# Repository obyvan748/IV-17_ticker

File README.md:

# IV-17_Ticker

## A ticker build from IV-17 tubes in a stackable manner

The idea is to build a ticker from IV-17 tubes wich should be able to be stacked to support a variable number of tube modules.

The ticker is made up from a main component und many client components. 
The main component give the high voltage power supply and the server component a home. 
The client components are made up from a tube and a dasy chanable electronic to drive the tube.

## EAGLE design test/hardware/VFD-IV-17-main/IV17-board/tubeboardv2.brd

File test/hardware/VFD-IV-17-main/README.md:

# VFD-IV-17
Schematics, board, and code for IV-17

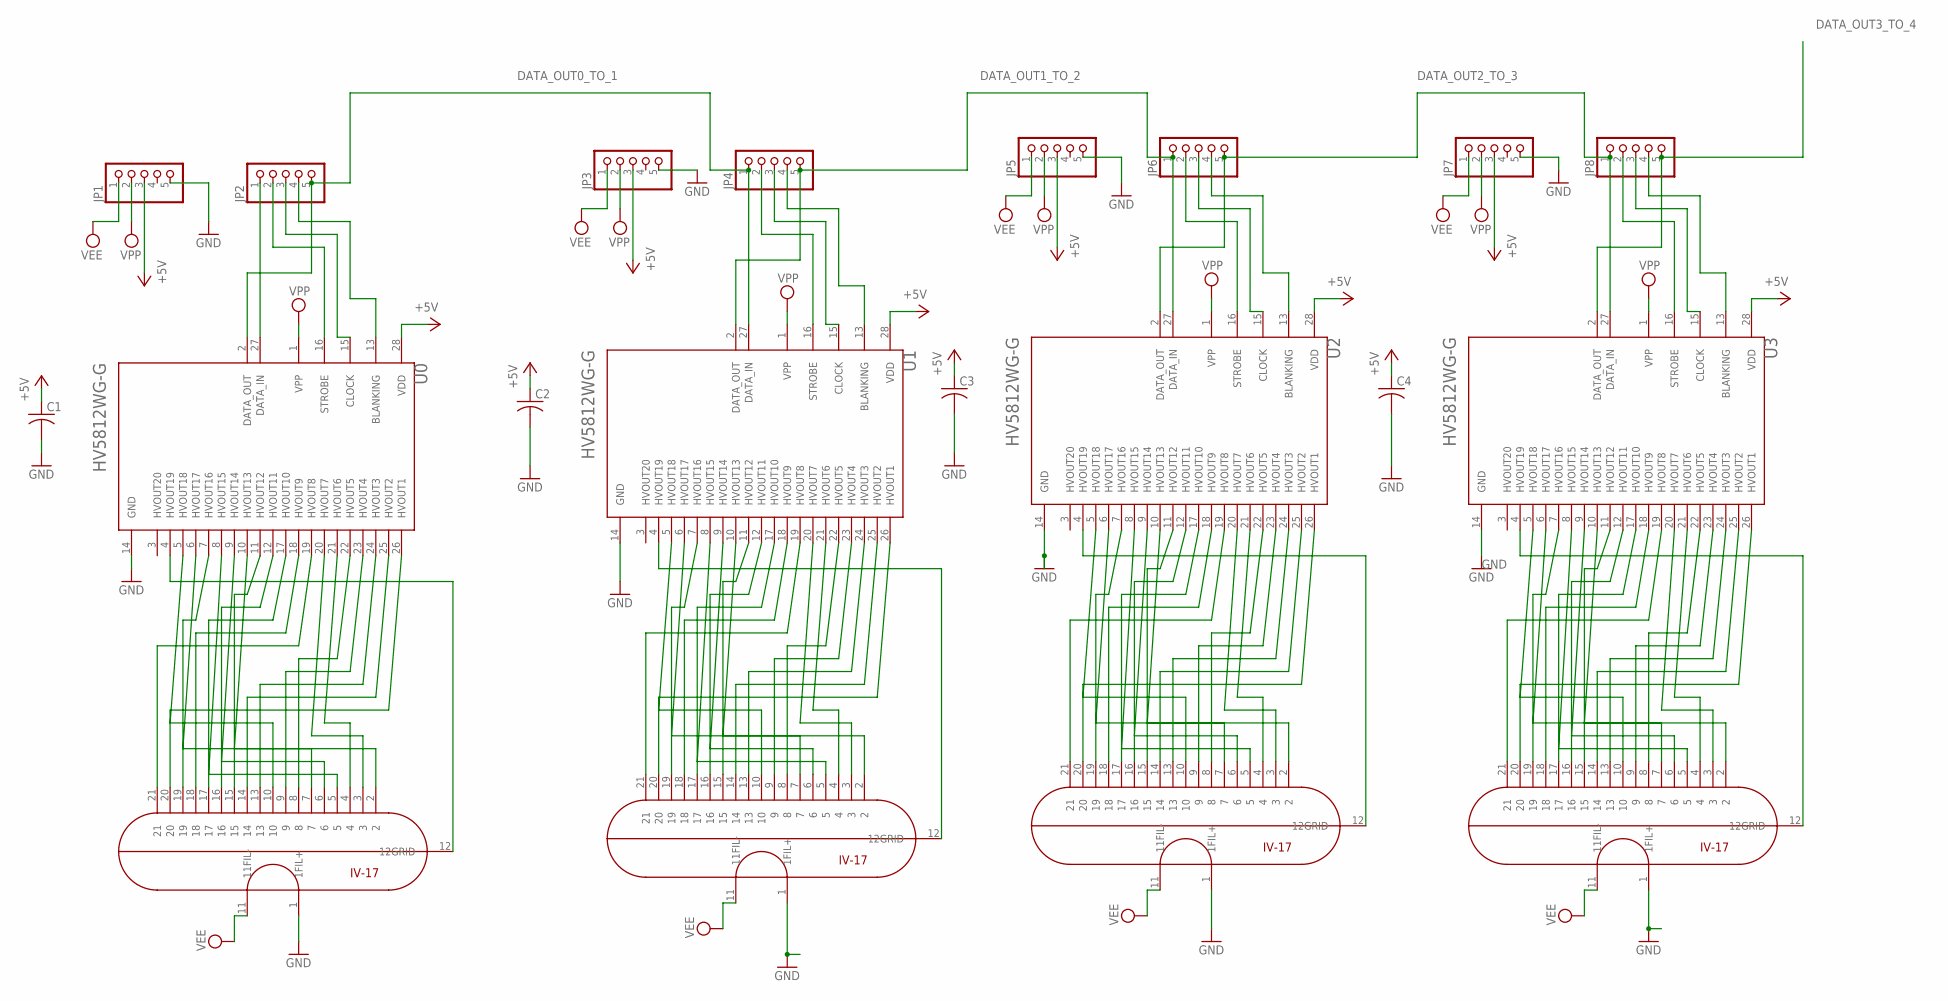
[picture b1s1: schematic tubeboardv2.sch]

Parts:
C1, C2, C3, C4: C-USC0805; C0805
IV0, IV1, IV2, IV3: IV17; NIXIE-22
JP1, JP2, JP3, JP4, JP5, JP6, JP7, JP8: PINHD-1X5; 1X05
U0, U1, U2, U3: MICROCHIP_HV5812WG-GMICROCHIP_HV5812WG-G_0_0; MICROCHIP_HV5812WG-G_0

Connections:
+5V: C1.1, C2.1, C3.1, C4.1, JP1.3, JP3.3, JP5.3, JP7.3, U0.28 (VDD), U1.28 (VDD), U2.28 (VDD), U3.28 (VDD)
BLANK: JP2.4, JP4.4, JP6.4, JP8.4, U0.13 (BLANKING), U1.13 (BLANKING), U2.13 (BLANKING), U3.13 (BLANKING)
CLOCK: JP2.3, JP4.3, JP6.3, JP8.3, U0.15 (CLOCK), U1.15 (CLOCK), U2.15 (CLOCK), U3.15 (CLOCK)
DATA_IN: JP2.1, U0.27 (DATA_IN)
DATA_OUT0_TO_1: JP2.5, JP4.1, U0.2 (DATA_OUT), U1.27 (DATA_IN)
DATA_OUT1_TO_2: JP4.5, JP6.1, U1.2 (DATA_OUT), U2.27 (DATA_IN)
DATA_OUT2_TO_3: JP6.5, JP8.1, U2.2 (DATA_OUT), U3.27 (DATA_IN)
DATA_OUT3_TO_4: JP8.5, U3.2 (DATA_OUT)
GND: C1.2, C2.2, C3.2, C4.2, IV0.1 (1FIL+), IV1.1 (1FIL+), IV2.1 (1FIL+), IV3.1 (1FIL+), JP1.5, JP3.5, JP5.5, JP7.5, U0.14 (GND), U1.14 (GND), U2.14 (GND), U3.14 (GND)
unnamed: IV0.20, U0.26 (HVOUT1)
unnamed: IV0.14, U0.25 (HVOUT2)
unnamed: IV0.13, U0.24 (HVOUT3)
unnamed: IV0.9, U0.23 (HVOUT4)
unnamed: IV0.8, U0.22 (HVOUT5)
unnamed: IV0.4, U0.21 (HVOUT6)
unnamed: IV0.3, U0.20 (HVOUT7)
unnamed: IV0.21, U0.19 (HVOUT8)
unnamed: IV0.18, U0.18 (HVOUT9)
unnamed: IV0.17, U0.17 (HVOUT10)
unnamed: IV0.16, U0.12 (HVOUT11)
unnamed: IV0.15, U0.11 (HVOUT12)
unnamed: IV0.7, U0.10 (HVOUT13)
unnamed: IV0.6, U0.9 (HVOUT14)
unnamed: IV0.5, U0.8 (HVOUT15)
unnamed: IV0.19, U0.7 (HVOUT16)
unnamed: IV0.2, U0.6 (HVOUT17)
unnamed: IV0.10, U0.5 (HVOUT18)
unnamed: IV0.12 (12GRID), U0.4 (HVOUT19)
unnamed: IV1.20, U1.26 (HVOUT1)
unnamed: IV1.14, U1.25 (HVOUT2)
unnamed: IV1.13, U1.24 (HVOUT3)
unnamed: IV1.9, U1.23 (HVOUT4)
unnamed: IV1.8, U1.22 (HVOUT5)
unnamed: IV1.4, U1.21 (HVOUT6)
unnamed: IV1.3, U1.20 (HVOUT7)
unnamed: IV1.21, U1.19 (HVOUT8)
unnamed: IV1.18, U1.18 (HVOUT9)
unnamed: IV1.17, U1.17 (HVOUT10)
unnamed: IV1.16, U1.12 (HVOUT11)
unnamed: IV1.15, U1.11 (HVOUT12)
unnamed: IV1.7, U1.10 (HVOUT13)
unnamed: IV1.6, U1.9 (HVOUT14)
unnamed: IV1.5, U1.8 (HVOUT15)
unnamed: IV1.19, U1.7 (HVOUT16)
unnamed: IV1.2, U1.6 (HVOUT17)
unnamed: IV1.10, U1.5 (HVOUT18)
unnamed: IV1.12 (12GRID), U1.4 (HVOUT19)
unnamed: IV2.20, U2.26 (HVOUT1)
unnamed: IV2.14, U2.25 (HVOUT2)
unnamed: IV2.13, U2.24 (HVOUT3)
unnamed: IV2.9, U2.23 (HVOUT4)
unnamed: IV2.8, U2.22 (HVOUT5)
unnamed: IV2.4, U2.21 (HVOUT6)
unnamed: IV2.3, U2.20 (HVOUT7)
unnamed: IV2.21, U2.19 (HVOUT8)
unnamed: IV2.18, U2.18 (HVOUT9)
unnamed: IV2.17, U2.17 (HVOUT10)
unnamed: IV2.16, U2.12 (HVOUT11)
unnamed: IV2.15, U2.11 (HVOUT12)
unnamed: IV2.7, U2.10 (HVOUT13)
unnamed: IV2.6, U2.9 (HVOUT14)
unnamed: IV2.5, U2.8 (HVOUT15)
unnamed: IV2.19, U2.7 (HVOUT16)
unnamed: IV2.2, U2.6 (HVOUT17)
unnamed: IV2.10, U2.5 (HVOUT18)
unnamed: IV2.12 (12GRID), U2.4 (HVOUT19)
unnamed: IV3.20, U3.26 (HVOUT1)
unnamed: IV3.14, U3.25 (HVOUT2)
unnamed: IV3.13, U3.24 (HVOUT3)
unnamed: IV3.9, U3.23 (HVOUT4)
unnamed: IV3.8, U3.22 (HVOUT5)
unnamed: IV3.4, U3.21 (HVOUT6)
unnamed: IV3.3, U3.20 (HVOUT7)
unnamed: IV3.21, U3.19 (HVOUT8)
unnamed: IV3.18, U3.18 (HVOUT9)
unnamed: IV3.17, U3.17 (HVOUT10)
unnamed: IV3.16, U3.12 (HVOUT11)
unnamed: IV3.15, U3.11 (HVOUT12)
unnamed: IV3.7, U3.10 (HVOUT13)
unnamed: IV3.6, U3.9 (HVOUT14)
unnamed: IV3.5, U3.8 (HVOUT15)
unnamed: IV3.19, U3.7 (HVOUT16)
unnamed: IV3.2, U3.6 (HVOUT17)
unnamed: IV3.10, U3.5 (HVOUT18)
unnamed: IV3.12 (12GRID), U3.4 (HVOUT19)
STROBE: JP2.2, JP4.2, JP6.2, JP8.2, U0.16 (STROBE), U1.16 (STROBE), U2.16 (STROBE), U3.16 (STROBE)
VEE: IV0.11 (11FIL-), IV1.11 (11FIL-), IV2.11 (11FIL-), IV3.11 (11FIL-), JP1.1, JP3.1, JP5.1, JP7.1
VPP: JP1.2, JP3.2, JP5.2, JP7.2, U0.1 (VPP), U1.1 (VPP), U2.1 (VPP), U3.1 (VPP)

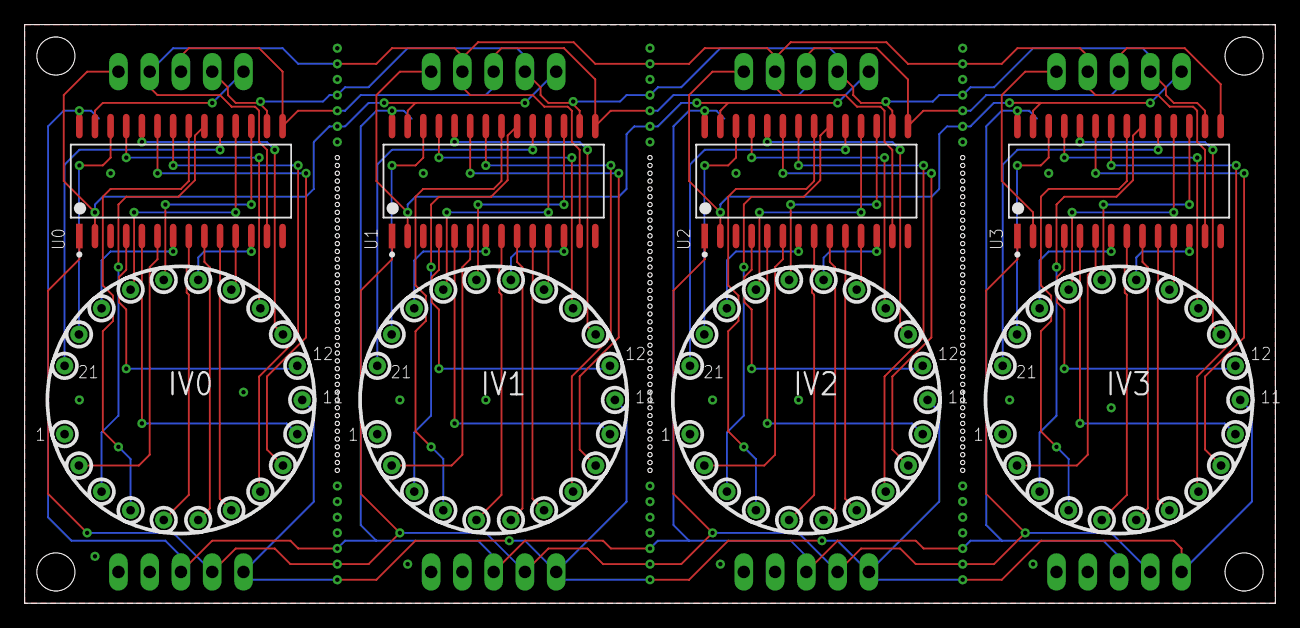
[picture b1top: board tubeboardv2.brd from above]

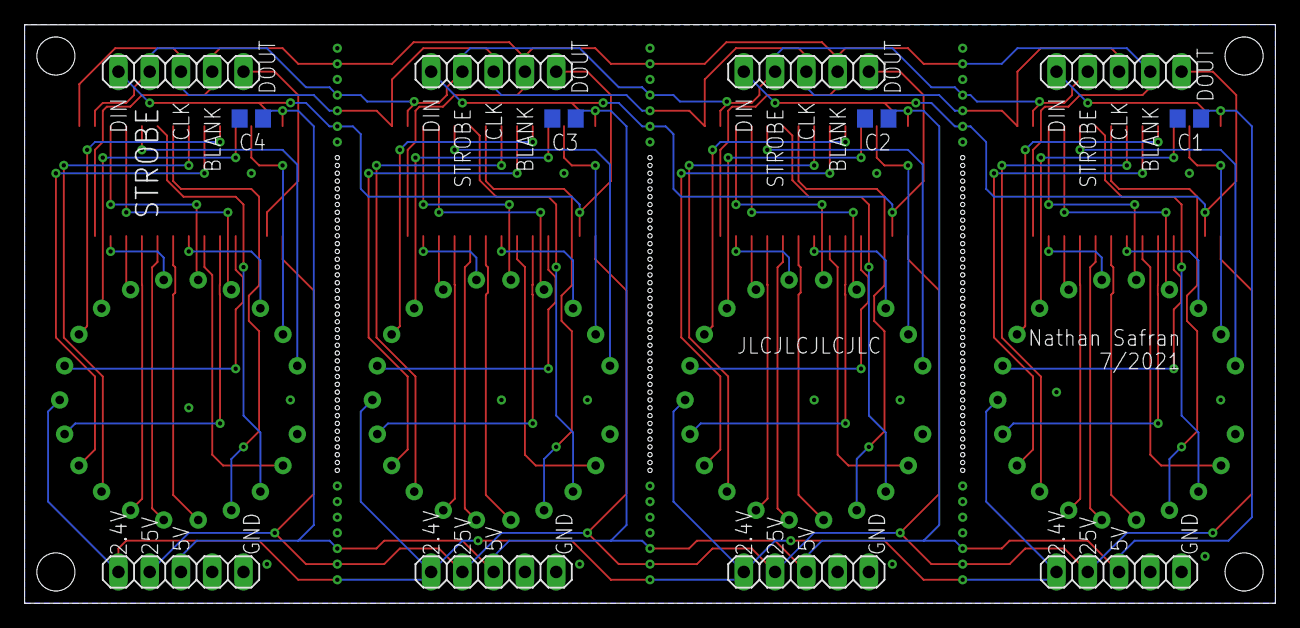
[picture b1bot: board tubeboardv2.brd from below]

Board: 2 copper layers, 101.6 x 47.0 mm, 20 parts (12 on the bottom side), 88 nets.

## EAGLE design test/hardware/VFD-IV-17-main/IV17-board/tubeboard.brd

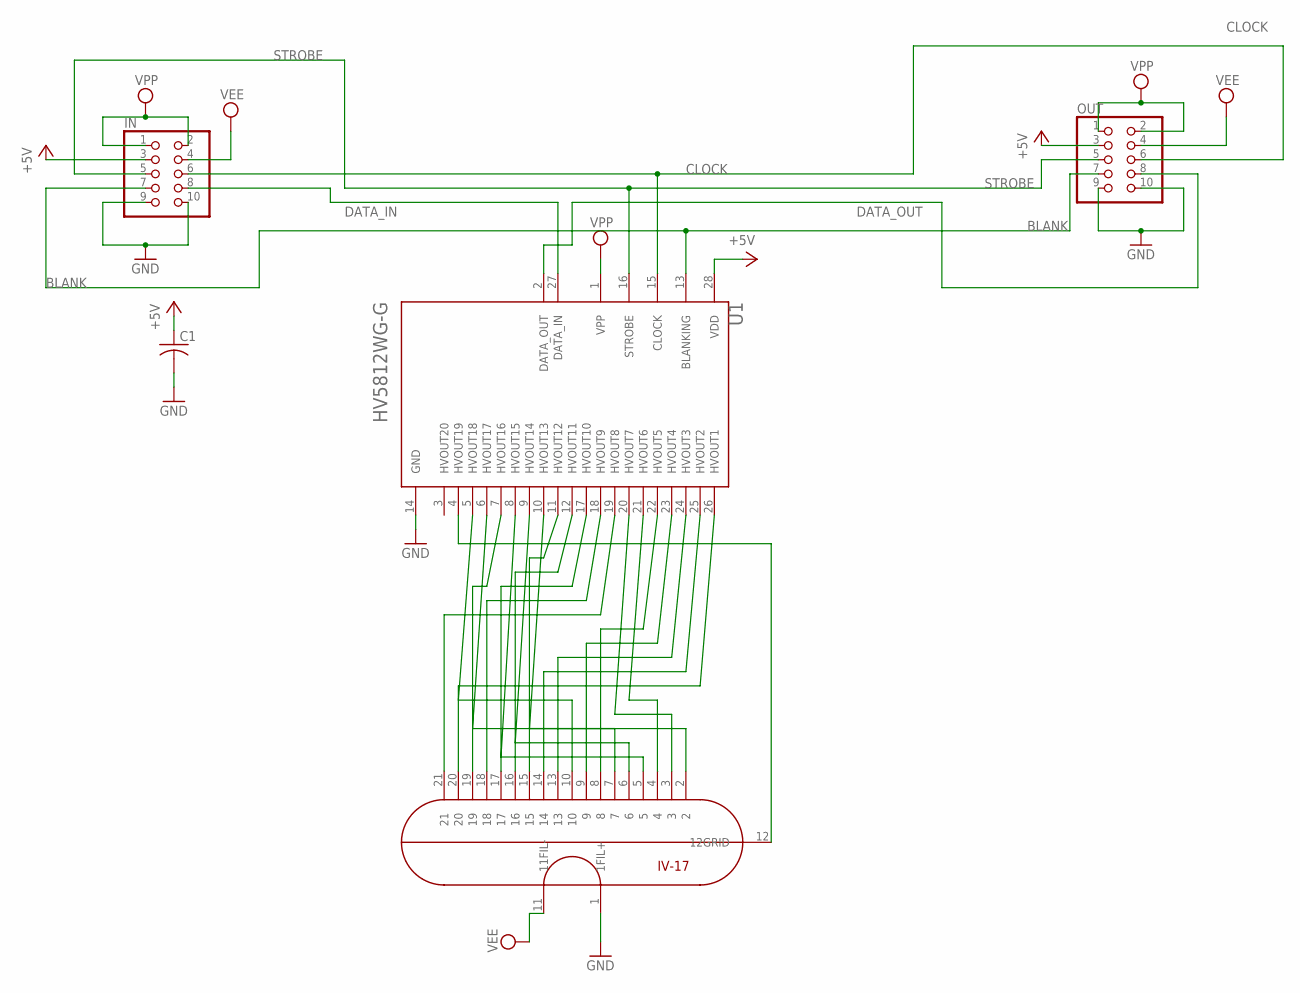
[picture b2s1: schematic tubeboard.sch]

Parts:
C1: C-USC0805; C0805
IN: PINHD-2X5/90; 2X05/90
IV17: IV17; NIXIE-22
OUT: PINHD-2X5/90; 2X05/90
U1: MICROCHIP_HV5812WG-GMICROCHIP_HV5812WG-G_0_0; MICROCHIP_HV5812WG-G_0

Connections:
+5V: C1.1, IN.3, OUT.3, U1.28 (VDD)
BLANK: IN.7, OUT.7, U1.13 (BLANKING)
CLOCK: IN.6, OUT.6, U1.15 (CLOCK)
DATA_IN: IN.8, U1.27 (DATA_IN)
DATA_OUT: OUT.8, U1.2 (DATA_OUT)
GND: C1.2, IN.9, IN.10, IV17.1 (1FIL+), OUT.9, OUT.10, U1.14 (GND)
unnamed: IV17.20, U1.26 (HVOUT1)
unnamed: IV17.14, U1.25 (HVOUT2)
unnamed: IV17.13, U1.24 (HVOUT3)
unnamed: IV17.9, U1.23 (HVOUT4)
unnamed: IV17.8, U1.22 (HVOUT5)
unnamed: IV17.4, U1.21 (HVOUT6)
unnamed: IV17.3, U1.20 (HVOUT7)
unnamed: IV17.21, U1.19 (HVOUT8)
unnamed: IV17.18, U1.18 (HVOUT9)
unnamed: IV17.17, U1.17 (HVOUT10)
unnamed: IV17.16, U1.12 (HVOUT11)
unnamed: IV17.15, U1.11 (HVOUT12)
unnamed: IV17.7, U1.10 (HVOUT13)
unnamed: IV17.6, U1.9 (HVOUT14)
unnamed: IV17.5, U1.8 (HVOUT15)
unnamed: IV17.19, U1.7 (HVOUT16)
unnamed: IV17.2, U1.6 (HVOUT17)
unnamed: IV17.10, U1.5 (HVOUT18)
unnamed: IV17.12 (12GRID), U1.4 (HVOUT19)
STROBE: IN.5, OUT.5, U1.16 (STROBE)
VEE: IN.4, IV17.11 (11FIL-), OUT.4
VPP: IN.1, IN.2, OUT.1, OUT.2, U1.1 (VPP)

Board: 2 copper layers, 5 parts (2 on the bottom side), 28 nets, no tracks yet.

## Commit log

2022-01-19 minor changes to README.md
2022-01-19 initial commit hw sw
2022-01-19 cleanup
